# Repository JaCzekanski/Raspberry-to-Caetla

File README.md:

# Raspberry PI Zero to Caetla (Xplorer) interface

Adapter for [Xplorer PS1 cartridges](https://github.com/simias/rustation/wiki/Xplorer-FX-setup) (for use with [catflap4linux](https://github.com/hkzlab/catflap4linux))

Author: Jakub Czekański

License: [CC BY 4.0](https://creativecommons.org/licenses/by/4.0)

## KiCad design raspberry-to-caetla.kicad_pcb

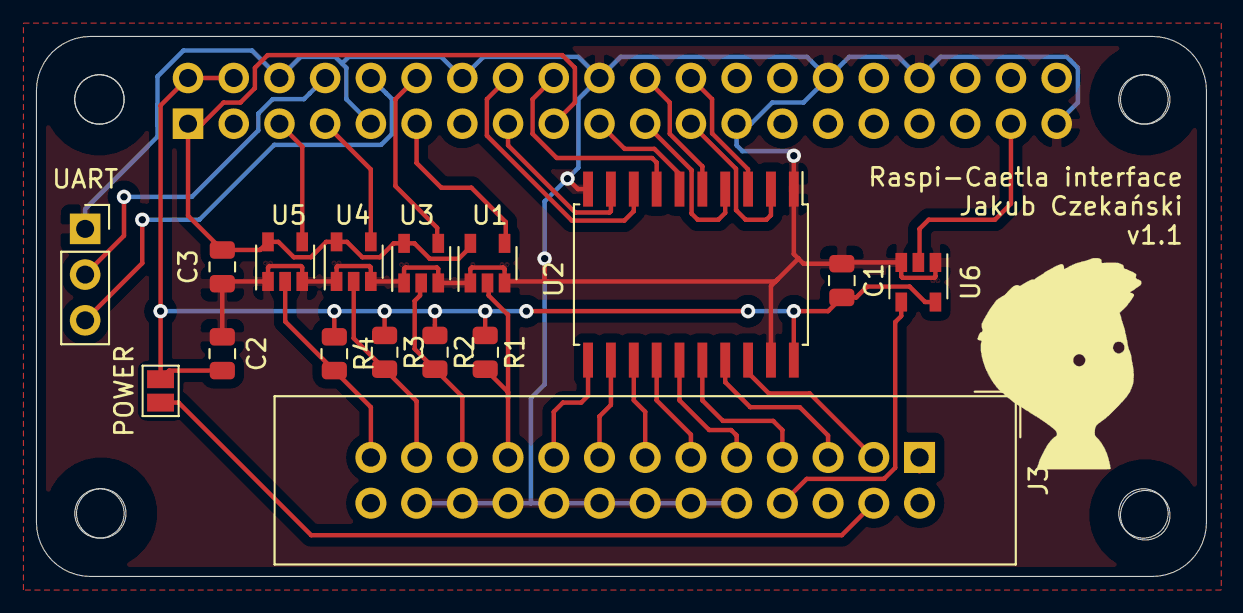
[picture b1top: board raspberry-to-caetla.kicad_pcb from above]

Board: 2 copper layers, 65.0 x 30.0 mm, 17 parts (1 on the bottom side), 32 nets.

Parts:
C1, C2, C3: 100n; C_0805_2012Metric
J2: RASPBERRY_PI; PinSocket_2x20_P2.54mm_Vertical
J3: PARALLEL; IDC-Header_2x13_P2.54mm_Vertical
POWER: 5V_PWR; SolderJumper-2_P1.3mm_Open_Pad1.0x1.5mm
R1, R2, R3, R4: 10k; R_0805_2012Metric
U1, U3, U4, U5, U6: 74LVC1G125; SOT-23-5
U2: 74HCT541; Infineon_PG-DSO-20-32
UART: UART; PinSocket_1x03_P2.54mm_Vertical

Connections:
+3V3: C3.1, J2.1, J2.17, U1.5, U3.5, U4.5, U5.5
+5V: C1.1, C2.1, J2.2, J2.4, POWER.1, R1.1, R2.1, R3.1, R4.1, U2.20, U6.5
/ACK: J3.19, R1.2, U1.2
/BUSY: J3.21, R2.2, U3.2
/D0: J3.3, U2.18
/D1: J3.5, U2.17
/D2: J3.7, U2.16
/D3: J3.9, U2.15
/D4: J3.11, U2.14
/D5: J3.13, U2.13
/D6: J3.15, U2.12
/D7: J3.17, U2.11
/ERROR: J3.4, POWER.2
/PAPER_OUT: J3.23, R3.2, U4.2
/SELECT: J3.25, R4.2, U5.2
/SELECT_PRINTER: J3.8, U6.4
GND: C1.2, C2.2, C3.2, J2.6, J2.9, J2.14, J2.20, J2.25, J2.30, J2.34, J2.39, J3.10, J3.12, J3.14, J3.16, J3.18, J3.20, J3.22, J3.24, U1.1, U1.3, U2.1, U2.10, U2.19, U3.1, U3.3, U4.1, U4.3, U5.1, U5.3, U6.1, U6.3, UART.1
GPIO26: J2.37, U6.2
unnamed: J2.8, UART.2
unnamed: J2.10, UART.3
unnamed: J2.5, U5.4
unnamed: J2.7, U4.4
unnamed: J2.11, U1.4
unnamed: J2.12, U3.4
unnamed: J2.15, U2.9
unnamed: J2.16, U2.8
unnamed: J2.18, U2.7
unnamed: J2.19, U2.6
unnamed: J2.21, U2.4
unnamed: J2.22, U2.5
unnamed: J2.23, U2.2
unnamed: J2.24, U2.3

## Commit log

2019-10-02 version 1.0
2019-10-10 version 1.1
2020-04-26 Added BOM
